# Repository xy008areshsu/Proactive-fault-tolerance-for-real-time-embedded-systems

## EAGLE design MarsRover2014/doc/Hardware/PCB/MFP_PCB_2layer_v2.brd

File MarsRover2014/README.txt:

This Simulink project contains the files for the Mathworks Mars Rover robot competition. The primary model of interest is the simulation model, but also included is a model for execution on an Arduino DUE. The Arduino model uses a number of S-functions for use of the peripherals, including the I2C interface for communication with a Raspberry Pi. More detail on each of these models and the robot itself is included in the project documentation.

================== Quick Start ==================
1. Open the project by double clicking the MakerFaire.prj file in MATLAB
2. Open SimulationModel.slx
3. Press Run to start simulation

================== Requirements ==================
MATLAB r2014a on Windows 7 with Simulink, Stateflow, and some other TBs (add full list here)
Arduino DUE Simulink support package
Install Arduino DUE Windows drivers (copied in support package install, but must be installed by hand)

================== Release Notes ==================

Feb 2015 v1.0 First Public Release

TODO list
- Fix PCB issues:
 - Reversed Power/GND pins on servo headers
 - Add protection diode on battery input
 - Add separate holes for each pushbutton/switch for easier wiring
 - Increase hole size for power module and power input wires

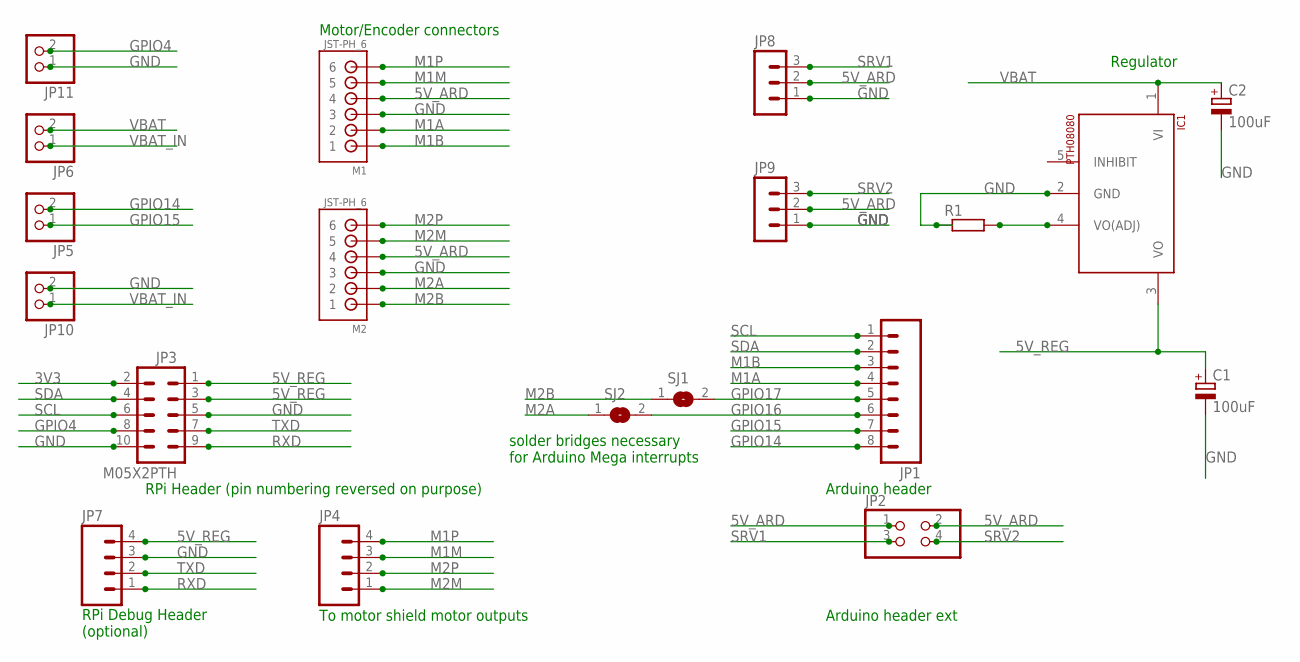
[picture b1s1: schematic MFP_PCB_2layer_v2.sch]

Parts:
C1, C2: 100uF; 150CLZ-0810
IC1: PTH08080
JP1: M08LONGPADS; 1X08_LONGPADS
JP2: PINHD-2X2; 2X02
JP3: M05X2PTH; AVR_ICSP
JP4, JP7: M04PTH; 1X04
JP5, JP6, JP10, JP11: PINHD-1X2; 1X02
JP8, JP9: MA03-1
M1, M2: JST-PH_6; JST_B6B-PH_HEADER
R1: R0204/7; 0204/7
SJ1, SJ2: SJ

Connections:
3V3: JP3.2
5V_ARD: JP2.1, JP2.2, JP8.2, JP9.2, M1.P4 (4), M2.P4 (4)
5V_REG: C1.+, IC1.3 (VO), JP3.1, JP3.3, JP7.4
GND: C1.-, C2.-, IC1.2 (GND), JP3.5, JP3.10, JP7.3, JP8.1, JP9.1, JP10.2, JP11.1, M1.P3 (3), M2.P3 (3), R1.1
GPIO4: JP3.8, JP11.2
GPIO14: JP1.8, JP5.2
GPIO15: JP1.7, JP5.1
GPIO16: JP1.6, SJ2.2
GPIO17: JP1.5, SJ1.2
M1A: JP1.4, M1.P2 (2)
M1B: JP1.3, M1.P1 (1)
M1M: JP4.3, M1.P5 (5)
M1P: JP4.4, M1.P6 (6)
M2A: M2.P2 (2), SJ2.1
M2B: M2.P1 (1), SJ1.1
M2M: JP4.1, M2.P5 (5)
M2P: JP4.2, M2.P6 (6)
unnamed: IC1.4 (VO(ADJ)), R1.2
RXD: JP3.9, JP7.1
SCL: JP1.1, JP3.6
SDA: JP1.2, JP3.4
SRV1: JP2.3, JP8.3
SRV2: JP2.4, JP9.3
TXD: JP3.7, JP7.2
VBAT: C2.+, IC1.1 (VI), JP6.2
VBAT_IN: JP6.1, JP10.1

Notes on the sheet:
To motor shield motor outputs
Arduino header
RPi Header (pin numbering reversed on purpose)
Motor/Encoder connectors
solder bridges necessary for Arduino Mega interrupts
RPi Debug Header (optional)
Regulator
Arduino header ext

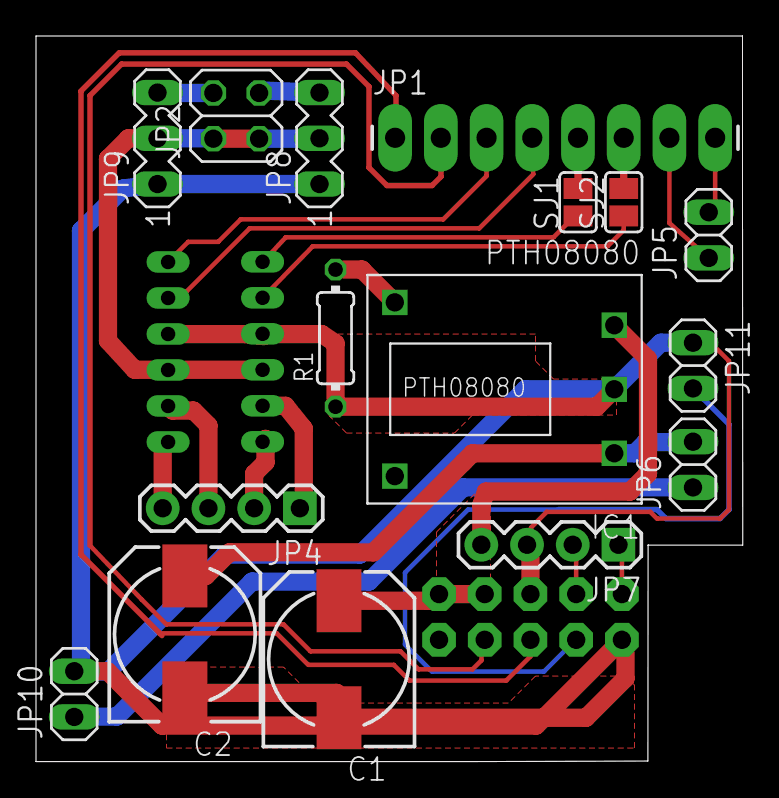
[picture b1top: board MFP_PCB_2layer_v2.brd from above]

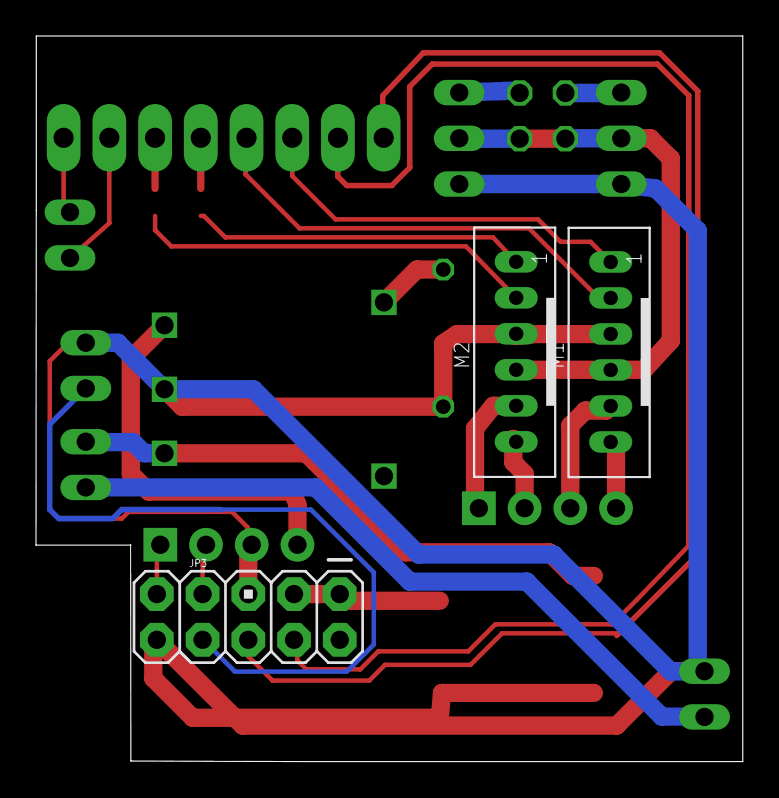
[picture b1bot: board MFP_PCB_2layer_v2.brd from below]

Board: 2 copper layers, 39.3 x 40.3 mm, 19 parts (3 on the bottom side), 25 nets.

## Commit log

2014-09-30 added src
2015-04-05 added more stuff

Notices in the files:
parts and their libraries:
SparkFun-Connectors: Licensing: Creative Commons ShareAlike 4.0 International - https://creativecommons.org/licenses/by-sa/4.0
